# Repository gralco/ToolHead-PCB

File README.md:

# ToolHead-PCB
Tool Head PCB Used for Automatic Swapping with Thermocouple Measurement and Data Storage in EEPROM

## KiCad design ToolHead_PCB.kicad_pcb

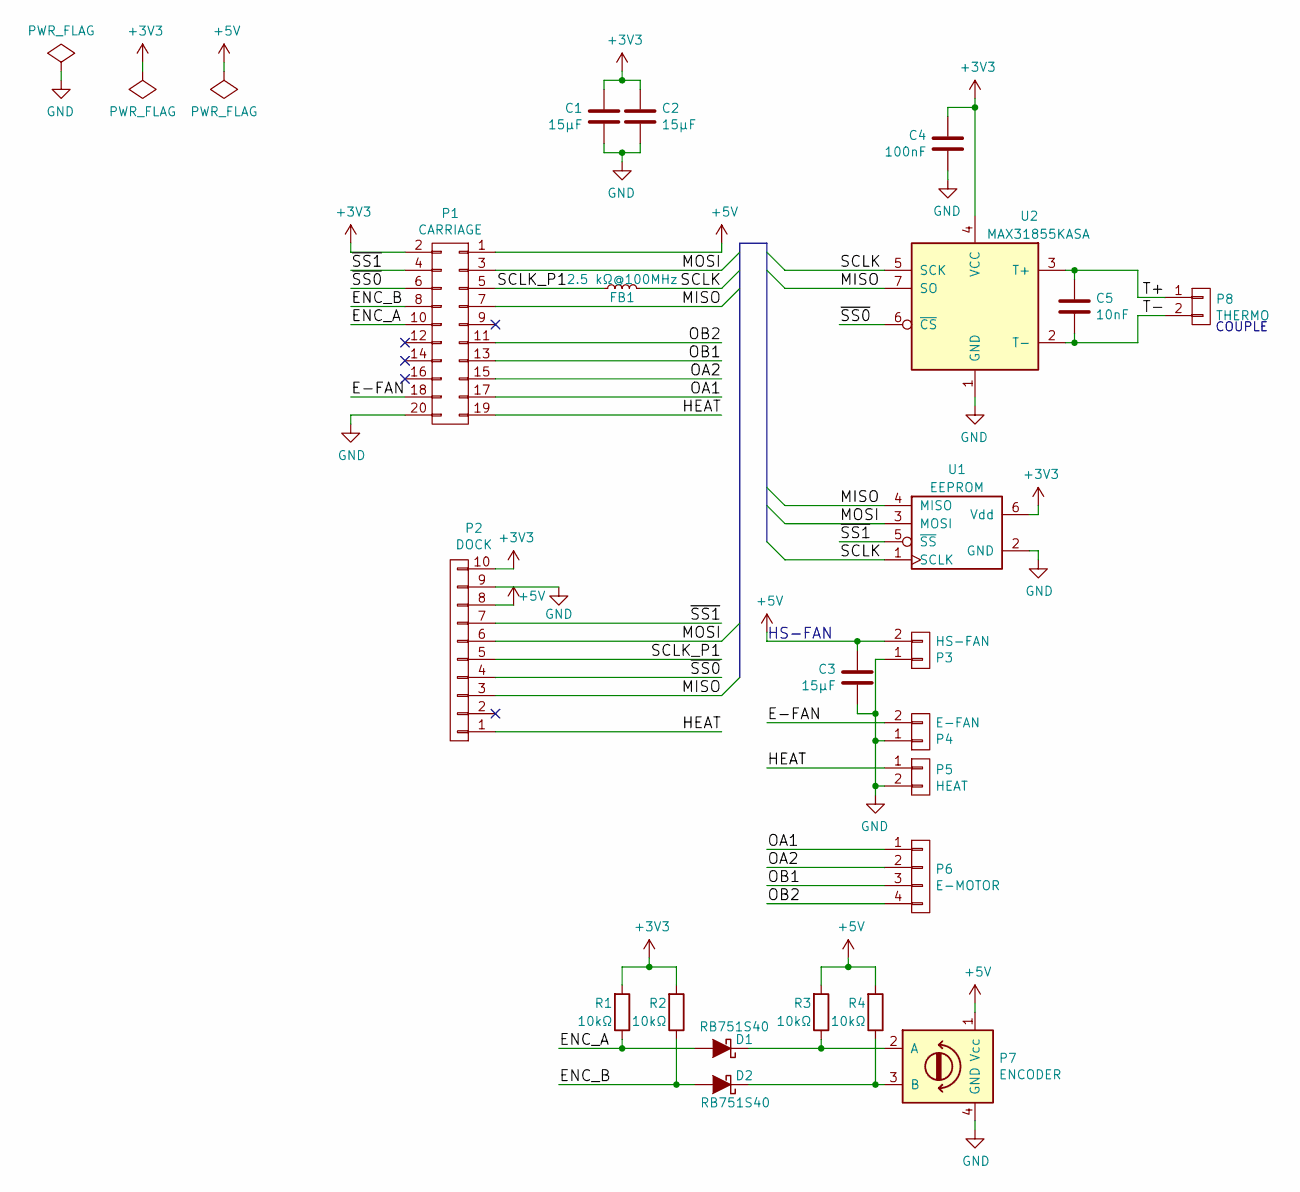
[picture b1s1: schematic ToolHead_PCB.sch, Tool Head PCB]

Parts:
C1, C2, C3: 15μF; C_0603_HandSoldering; Tolerance 20%; MFG Part Num C1608X5R0J156M080AC
C4: 100nF; C_0603_HandSoldering; Tolerance 10%; MFG Part Num GRM188R71H104KA93D
C5: 10nF; C_0603_HandSoldering; Tolerance 5%; MFG Part Num C0603C103J5RACTU
D1, D2: RB751S40; SOD-523F; MFG Part Num RB751S40
FB1: 2.5 kΩ@100MHz; C_0603; MFG Part Num BK1608LM252-T
P1: CARRIAGE; Pin_Header_Angled_2x10; MFG Part Num 499-10-220-10-007000
P2: DOCK; Pin_Header_Angled_1x10; MFG Part Num 399-10-110-10-007000
P3: HS-FAN; Pin_Header_Angled_1x02; MFG Part Num 0705530001
P4: E-FAN; Pin_Header_Angled_1x02; MFG Part Num 0705530001
P5: HEAT; Pin_Header_Angled_1x02; MFG Part Num 0705530001
P6: E-MOTOR; Pin_Header_Angled_1x04; MFG Part Num 0705530003
P7: ENCODER; Pin_Header_Angled_1x04; MFG Part Num 0705530003
P8: THERMO; THERMOCOUPLE
R1, R2, R3, R4: 10kΩ; R_0603_HandSoldering; Tolerance 1%; MFG Part Num RC0603FR-0710KL
U1: EEPROM; SOT-23-6; MFG Part Num 25AA02UIDT-I/OT
U2: MAX31855KASA; SO-8; MFG Part Num MAX31855KASA+

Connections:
+3V3: C1.1, C2.1, C4.1, P1.2, P2.10, R1.2, R2.2, U1.6 (Vdd), U2.4 (VCC)
+5V: C3.1, P1.1, P2.8, P3.2, P7.1 (Vcc), R3.2, R4.2
/E-FAN: P1.18, P4.2
/ENC_A: D1.2 (A), P1.10, R1.1
/ENC_B: D2.2 (A), P1.8, R2.1
/HEAT: P1.19, P2.1, P5.1
/MISO: P1.7, P2.3, U1.4 (MISO), U2.7 (SO)
/MOSI: P1.3, P2.6, U1.3 (MOSI)
/OA1: P1.17, P6.1
/OA2: P1.15, P6.2
/OB1: P1.13, P6.3
/OB2: P1.11, P6.4
/SCLK: FB1.2, U1.1 (SCLK), U2.5 (SCK)
/SCLK_P1: FB1.1, P1.5, P2.5
/T+: C5.1, P8.1, U2.3 (T+)
/T-: C5.2, P8.2, U2.2 (T-)
/~SS0: P1.6, P2.4, U2.6 (~CS~)
/~SS1: P1.4, P2.7, U1.5 (~SS)
GND: C1.2, C2.2, C3.2, C4.2, P1.20, P2.9, P3.1, P4.1, P5.2, P7.4 (GND), U1.2 (GND), U2.1 (GND)
unnamed: D1.1 (K), P7.2 (A), R3.1
unnamed: D2.1 (K), P7.3 (B), R4.1

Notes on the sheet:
HS-FAN
COUPLE

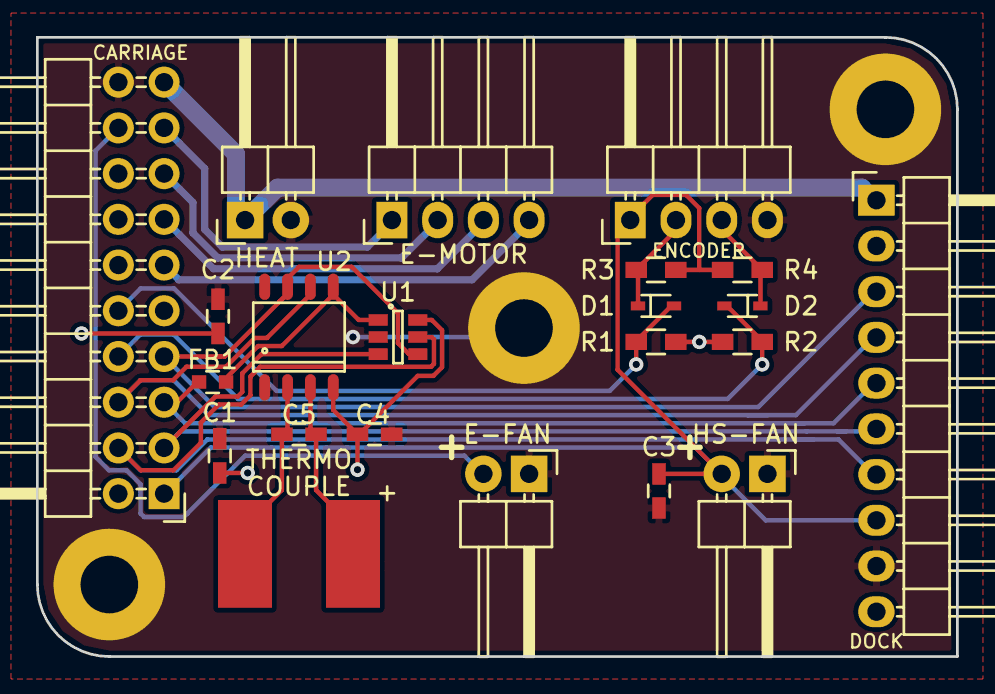
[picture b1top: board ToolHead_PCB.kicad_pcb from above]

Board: 2 copper layers, 51.1 x 34.4 mm, 22 parts (0 on the bottom side), 21 nets.

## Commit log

2017-10-08 Add all project files

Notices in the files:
ToolHead_PCB.kicad_pcb:
GNU GPLv3, Copyright 2016-2017
GNU GPLv3
